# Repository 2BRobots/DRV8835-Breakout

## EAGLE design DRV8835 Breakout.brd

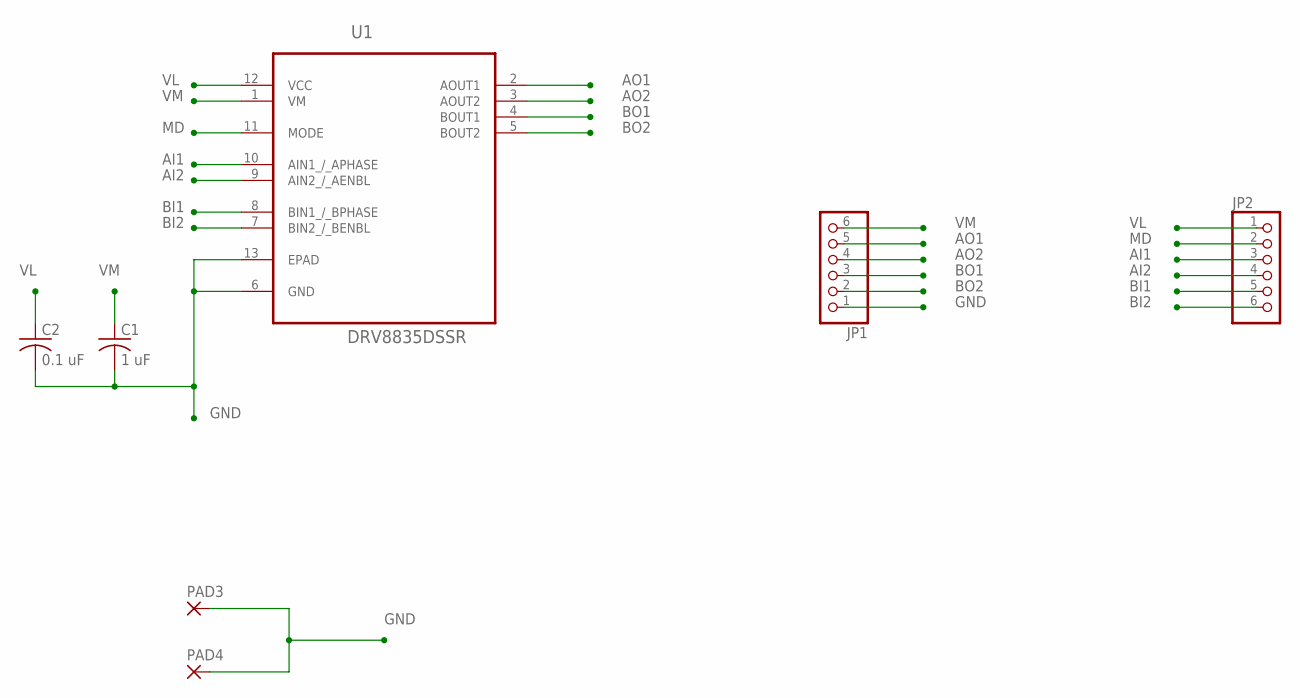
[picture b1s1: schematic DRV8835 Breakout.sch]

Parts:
C1: 1 uF; C0603K
C2: 0.1 uF; C0603K
JP1, JP2: PINHD-1X6CLEAN; 1X06-CLEAN
PAD3, PAD4: SMD2; SMD1,27-2,54
U1: DRV8835DSSR; SON50P200X300X80-13N

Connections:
AI1: JP2.3, U1.10 (AIN1_/_APHASE)
AI2: JP2.4, U1.9 (AIN2_/_AENBL)
AO1: JP1.5, U1.2 (AOUT1)
AO2: JP1.4, U1.3 (AOUT2)
BI1: JP2.5, U1.8 (BIN1_/_BPHASE)
BI2: JP2.6, U1.7 (BIN2_/_BENBL)
BO1: JP1.3, U1.4 (BOUT1)
BO2: JP1.2, U1.5 (BOUT2)
GND: C1.2, C2.2, JP1.1, PAD3.1, PAD4.1, U1.6 (GND), U1.13 (EPAD)
MD: JP2.2, U1.11 (MODE)
VL: C2.1, JP2.1, U1.12 (VCC)
VM: C1.1, JP1.6, U1.1 (VM)

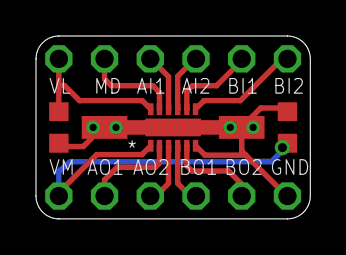
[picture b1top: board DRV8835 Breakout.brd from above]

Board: 2 copper layers, 15.2 x 10.2 mm, 7 parts (0 on the bottom side), 12 nets.

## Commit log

2016-08-02 added eagle files

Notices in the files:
DRV8835 Breakout.brd:
CC-BY-SA
